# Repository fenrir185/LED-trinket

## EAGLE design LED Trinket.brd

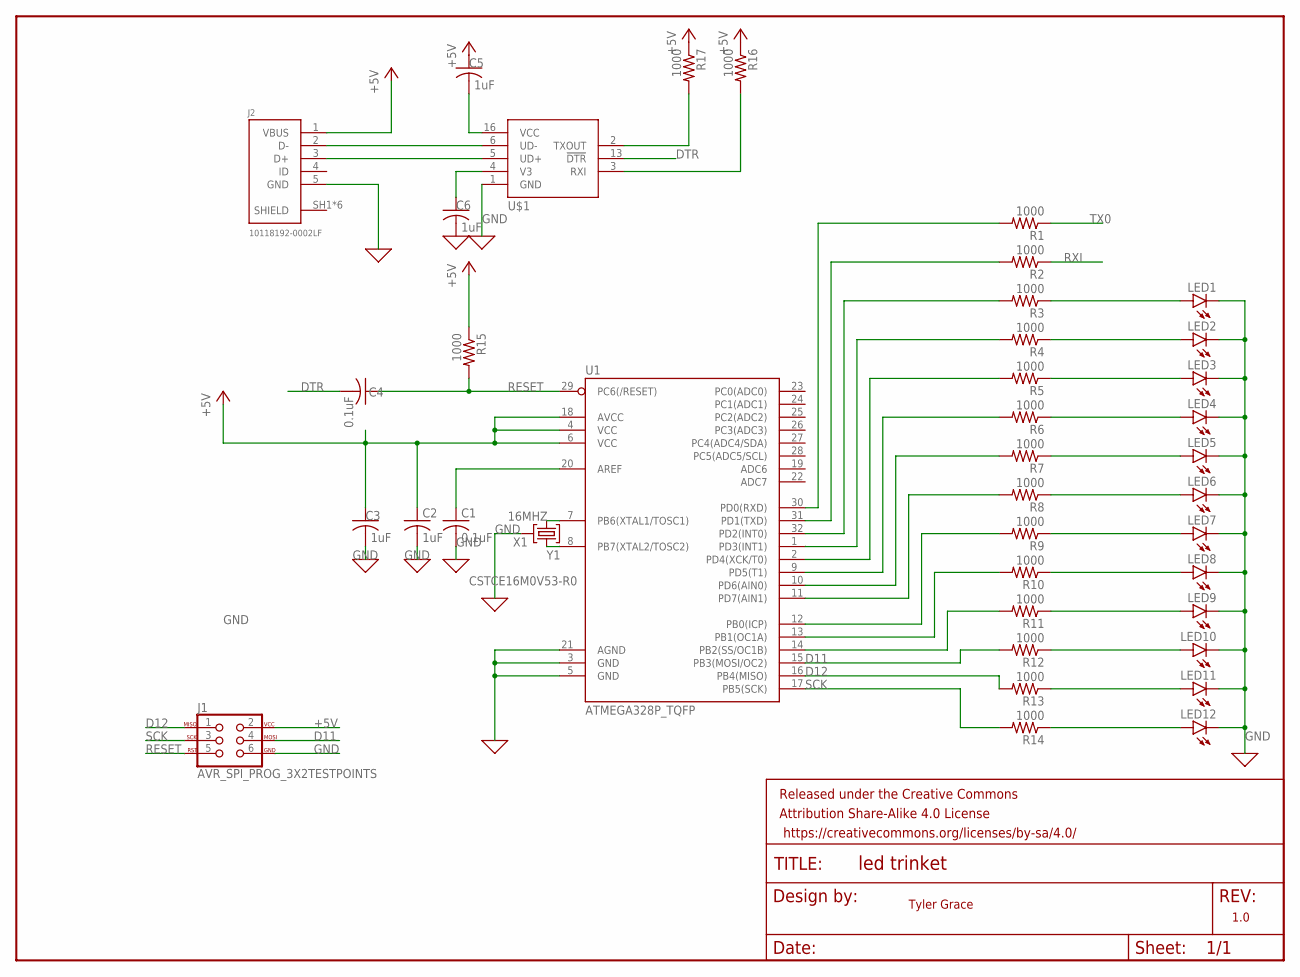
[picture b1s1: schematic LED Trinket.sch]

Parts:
C1, C4: 0.1uF; C0805
C2, C3, C5, C6: 1uF; C0805
FRAME1: FRAME-LETTERNO_PACKAGE; DUMMY
J1: AVR_SPI_PROG_3X2TESTPOINTS; 2X3_TEST_POINTS
J2: 10118192-0002LF
LED1, LED2, LED3, LED4, LED5, LED6, LED7, LED8, LED9, LED10, LED11, LED12: LED; SMARTLED-TTW
R1, R2, R3, R4, R5, R6, R7, R8, R9, R10, R11, R12, R13, R14, R15, R16, R17: 1000; R0805
U1: ATMEGA328P_TQFP; TQFP32-08
U$1: CH340C; SOP-16
X1: CSTCE16M0V53-R0

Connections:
0: C6.2
16MHZ: U1.7 (PB6(XTAL1/TOSC1)), X1.1 (INPUT)
+5V: C2.1, C3.1, C5.1, J1.2, J2.1 (VBUS), R15.1, R16.1, R17.1, U1.4 (VCC), U1.6 (VCC), U1.18 (AVCC)
D11: J1.4, R12.2, U1.15 (PB3(MOSI/OC2))
D12: J1.1, R13.2, U1.16 (PB4(MISO))
DTR: C4.2, U$1.13 (!DTR)
GND: C1.2, C2.2, C3.2, J1.6, J2.5 (GND), LED1.C@1 (C), LED2.C@1 (C), LED3.C@1 (C), LED4.C@1 (C), LED5.C@1 (C), LED6.C@1 (C), LED7.C@1 (C), LED8.C@1 (C), LED9.C@1 (C), LED10.C@1 (C), LED11.C@1 (C), LED12.C@1 (C), U$1.1 (GND), X1.2 (GND)
GROUND: U1.3 (GND), U1.5 (GND), U1.21 (AGND)
unnamed: R1.2, U1.30 (PD0(RXD))
unnamed: R2.2, U1.31 (PD1(TXD))
unnamed: C1.1, U1.20 (AREF)
unnamed: J2.2 (D-), U$1.6 (UD-)
unnamed: R3.2, U1.32 (PD2(INT0))
unnamed: R4.2, U1.1 (PD3(INT1))
unnamed: R5.2, U1.2 (PD4(XCK/T0))
unnamed: R6.2, U1.9 (PD5(T1))
unnamed: R7.2, U1.10 (PD6(AIN0))
unnamed: R8.2, U1.11 (PD7(AIN1))
unnamed: R9.2, U1.12 (PB0(ICP))
unnamed: R10.2, U1.13 (PB1(OC1A))
unnamed: R11.2, U1.14 (PB2(SS/OC1B))
unnamed: J2.3 (D+), U$1.5 (UD+)
unnamed: C5.2, U$1.16 (VCC)
unnamed: C6.1, U$1.4 (V3)
unnamed: LED1.A@1 (A), R3.1
unnamed: LED2.A@1 (A), R4.1
unnamed: LED3.A@1 (A), R5.1
unnamed: LED4.A@1 (A), R6.1
unnamed: LED5.A@1 (A), R7.1
unnamed: LED6.A@1 (A), R8.1
unnamed: LED7.A@1 (A), R9.1
unnamed: LED8.A@1 (A), R10.1
unnamed: LED9.A@1 (A), R11.1
unnamed: LED10.A@1 (A), R12.1
unnamed: LED11.A@1 (A), R13.1
unnamed: LED12.A@1 (A), R14.1
unnamed: R17.2, U$1.2 (TXOUT)
unnamed: R16.2, U$1.3 (RXI)
RESET: C4.1, J1.5, R15.2, U1.29 (PC6(/RESET))
RXI: R2.1
SCK: J1.3, R14.2, U1.17 (PB5(SCK))
SHIELD: J2.SH1 (SHIELD), J2.SH2 (SHIELD), J2.SH3 (SHIELD), J2.SH4 (SHIELD), J2.SH5 (SHIELD), J2.SH6 (SHIELD)
TX0: R1.1
Y1: U1.8 (PB7(XTAL2/TOSC2)), X1.3 (OUTPUT)

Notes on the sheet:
Tyler Grace
1.0

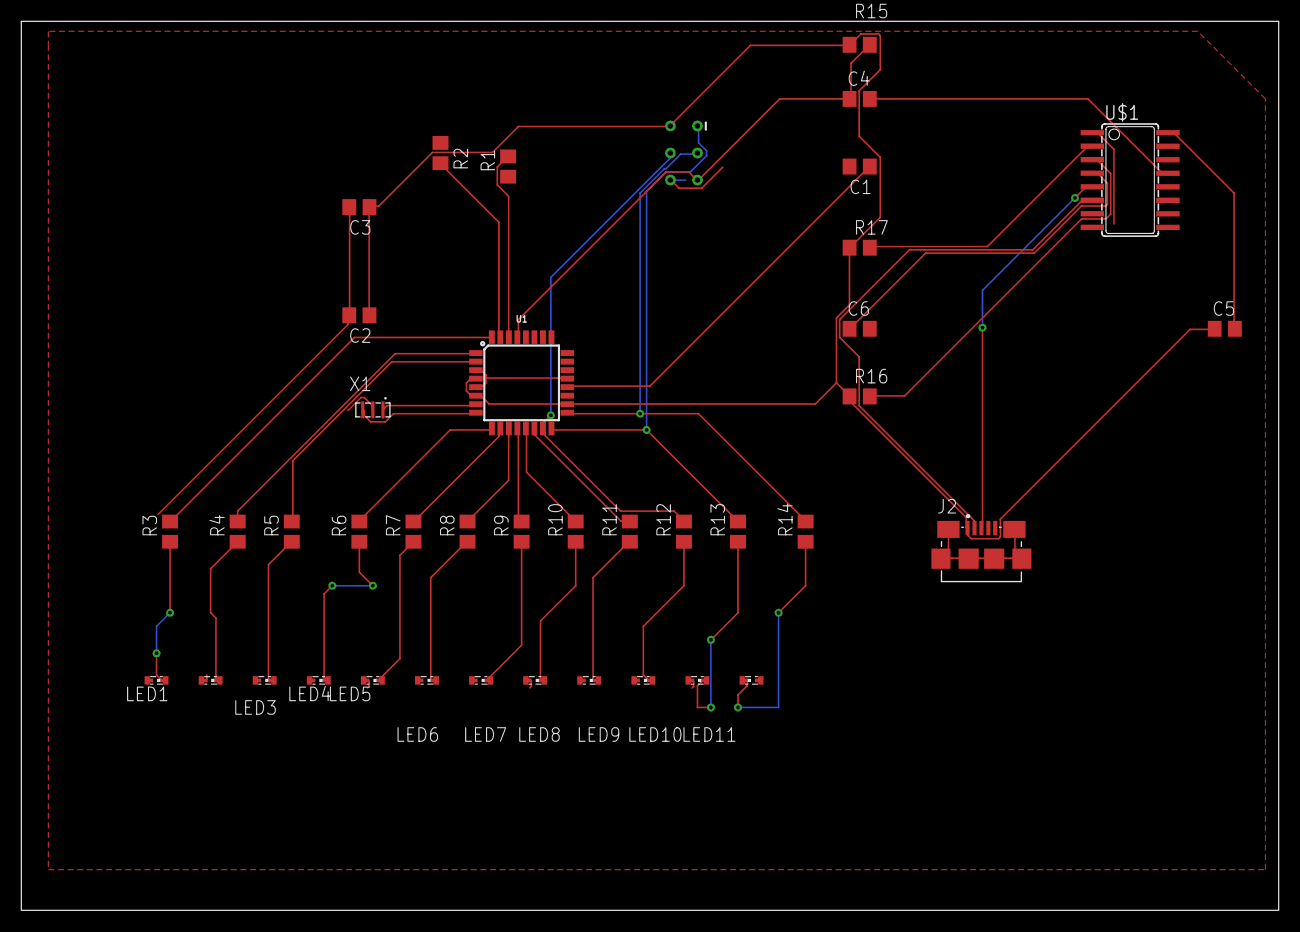
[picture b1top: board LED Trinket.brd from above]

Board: 2 copper layers, 118.1 x 83.5 mm, 41 parts (1 on the bottom side), 41 nets.

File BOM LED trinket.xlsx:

Part | Value | Device | Package | Description | Price | Lead time
C1 | 0.1uF | C-USC0805 | C0805 | CAPACITOR, American symbol | 3.98 | 1-5 days
C2 | 1uF | C-USC0805 | C0805 | CAPACITOR, American symbol | 1.1000000000000001 | 1-5 days
C3 | 1uF | C-USC0805 | C0805 | CAPACITOR, American symbol | 1.1000000000000001 | 1-5 days
C4 | 0.1uF | C-USC0805 | C0805 | CAPACITOR, American symbol | 3.98 | 1-5 days
C5 | 1uF | C-USC0805 | C0805 | CAPACITOR, American symbol | 1.1000000000000001 | 1-5 days
C6 | .1uF | C-USC0805 | C0805 | CAPACITOR, American symbol | 3.98 | 1-5 days
J1 | AVR_SPI_PR | AVR_SPI_PROG_3X2TESTPOINTS | 2X3_TEST_POINTS | AVR ISP 6 Pin
J2 | 10118192-0 | 10118192-0002LF | 10118192-0002LF | CONN RCPT USB2.0 MICRO B SMD R/A |  | 1-5 days
LED1 |  | LED | SMARTLED-TTW | LED | 0.98 | 1-5 days
LED2 |  | LED | SMARTLED-TTW | LED | 0.98 | 1-5 days
LED3 |  | LED | SMARTLED-TTW | LED | 0.98 | 1-5 days
LED4 |  | LED | SMARTLED-TTW | LED | 0.98 | 1-5 days
LED5 |  | LED | SMARTLED-TTW | LED | 0.98 | 1-5 days
LED6 |  | LED | SMARTLED-TTW | LED | 0.98 | 1-5 days
LED7 |  | LED | SMARTLED-TTW | LED | 0.98 | 1-5 days
LED8 |  | LED | SMARTLED-TTW | LED | 0.98 | 1-5 days
LED9 |  | LED | SMARTLED-TTW | LED | 0.98 | 1-5 days
LED10 |  | LED | SMARTLED-TTW | LED | 0.98 | 1-5 days
LED11 |  | LED | SMARTLED-TTW | LED | 0.98 | 1-5 days
LED12 |  | LED | SMARTLED-TTW | LED | 0.98 | 1-5 days
R1 | 1000 | R-US_R0805 | R0805 | RESISTOR, American symbol | 0.56000000000000005 | 1-5 days
R2 | 1000 | R-US_R0805 | R0805 | RESISTOR, American symbol | 0.56000000000000005 | 1-5 days
R3 | 1000 | R-US_R0805 | R0805 | RESISTOR, American symbol | 0.56000000000000005 | 1-5 days
R4 | 1000 | R-US_R0805 | R0805 | RESISTOR, American symbol | 0.56000000000000005 | 1-5 days
R5 | 1000 | R-US_R0805 | R0805 | RESISTOR, American symbol | 0.56000000000000005 | 1-5 days
R6 | 1000 | R-US_R0805 | R0805 | RESISTOR, American symbol | 0.56000000000000005 | 1-5 days
R7 | 1000 | R-US_R0805 | R0805 | RESISTOR, American symbol | 0.56000000000000005 | 1-5 days
R8 | 1000 | R-US_R0805 | R0805 | RESISTOR, American symbol | 0.56000000000000005 | 1-5 days
R9 | 1000 | R-US_R0805 | R0805 | RESISTOR, American symbol | 0.56000000000000005 | 1-5 days
R10 | 1000 | R-US_R0805 | R0805 | RESISTOR, American symbol | 0.56000000000000005 | 1-5 days
R11 | 1000 | R-US_R0805 | R0805 | RESISTOR, American symbol | 0.56000000000000005 | 1-5 days
R12 | 1000 | R-US_R0805 | R0805 | RESISTOR, American symbol | 0.56000000000000005 | 1-5 days
R13 | 1000 | R-US_R0805 | R0805 | RESISTOR, American symbol | 0.56000000000000005 | 1-5 days
R14 | 1000 | R-US_R0805 | R0805 | RESISTOR, American symbol | 0.56000000000000005 | 1-5 days
R15 | 1000 | R-US_R0805 | R0805 | RESISTOR, American symbol | 0.56000000000000005 | 1-5 days
R16 | 1000 | R-US_R0805 | R0805 | RESISTOR, American symbol | 0.56000000000000005 | 1-5 days
R17 | 1000 | R-US_R0805 | R0805 | RESISTOR, American symbol | 0.56000000000000005 | 1-5 days
U$1 | CH340C | CH340C | SOP-16 | CH340C USB TO UART IC | 2.59 | 30-50 days
U1 | ATMEGA328P | ATMEGA328P_TQFP | TQFP32-08 | Popular 328P in QFP | 2.11 | 1-5 days
X1 | CSTCE16M0V | CSTCE16M0V53-R0 | CSTCE16M0V53-R0 | CER RES 16.0000MHZ 15PF SMD | &0.39 | 1-5 days
Board | 4.65 x 3.29 inches | 2 layer board |  |  | 76.5 | 9-12 days

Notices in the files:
parts and their libraries:
SparkFun-Aesthetics: Licensing: Creative Commons ShareAlike 4.0 International - https://creativecommons.org/licenses/by-sa/4.0
SparkFun-Aesthetics: Released under the Creative Commons Attribution Share-Alike 4.0 License
SparkFun-Aesthetics: https://creativecommons.org/licenses/by-sa/4.0
